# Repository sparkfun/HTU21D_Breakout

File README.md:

**NOTE:** *This product has been retired from our catalog. If you are looking for more up-to-date info, please check out some of these resources to see how other users are still hacking and improving on this product.*
* *[SparkFun Forum](https://forum.sparkfun.com/)*
* *[Comments Here on GitHub](https://github.com/sparkfun/HTU21D_Breakout/issues)*

*We recommend looking at the [Si7021](https://www.sparkfun.com/products/13763), which is a drop-in replacement for the HTU21D. It uses the same address and methods to read the sensor.*

SparkFun Humidity and Temperature Sensor Breakout - HTU21D
===========================================================

[*SparkFun Humidity and Temperature Sensor Breakout - HTU21D (SEN-12064)*](https://www.sparkfun.com/products/12064)

This is a breadboard friendly breakout board for the Measurement Specialties high-precision, low-power digital humidity sensor.

Repository Contents
-------------------
* **/Firmware** - Example code 
* **/Hardware** - Eagle design files (.brd, .sch)
* **/Libraries** - Libraries for use with the <PRODUCT NAME>
* **/Production** - Production panel files (.brd)

Documentation
--------------
* **[Library](https://github.com/sparkfun/SparkFun_HTU21D_Breakout_Arduino_Library)** - Arduino library for the HTU21D.
* **[Hookup Guide](https://learn.sparkfun.com/tutorials/htu21d-humidity-sensor-hookup-guide)** - Basic hookup guide for the HTU21D.
* **[SparkFun Fritzing repo](https://github.com/sparkfun/Fritzing_Parts)** - Fritzing diagrams for SparkFun products.
* **[SparkFun 3D Model repo](https://github.com/sparkfun/3D_Models)** - 3D models of SparkFun products. 

License Information
-------------------
This product is _**open source**_! 

The **hardware** is released under [Creative Commons ShareAlike 4.0 International](https://creativecommons.org/licenses/by-sa/4.0/).

The **code** is beerware; if you see me (or any other SparkFun employee) at the local, and you've found our code helpful, please buy us a round!

Please use, reuse, and modify these files as you see fit. Please maintain attribution to SparkFun Electronics and release anything derivative under the same license.

Distributed as-is; no warranty is given.

- Your friends at SparkFun.

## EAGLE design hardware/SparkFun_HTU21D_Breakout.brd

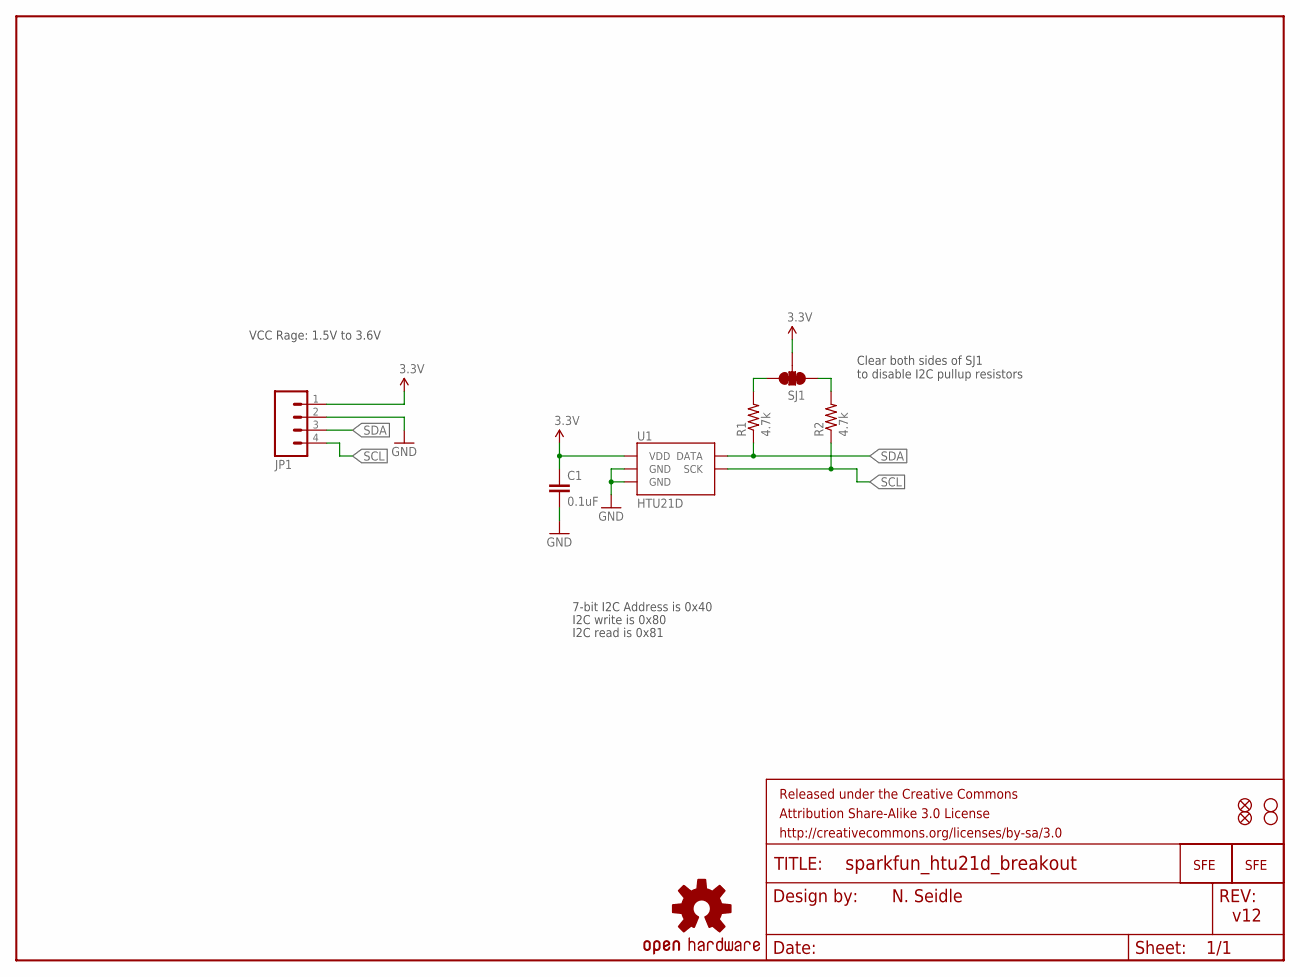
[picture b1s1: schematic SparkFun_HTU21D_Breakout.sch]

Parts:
C1: 0.1uF; 0603-CAP
FRAME2: FRAME-LETTER; CREATIVE_COMMONS
JP1: M04PTH; 1X04
JP2: LOGO-SFENW2; SFE-NEW-WEB
JP3, JP4: FIDUCIALUFIDUCIAL; MICRO-FIDUCIAL
LOGO1: LOGO-SFESK; SFE-LOGO-FLAME
LOGO2: OSHW-LOGOS; OSHW-LOGO-S
R1, R2: 4.7k; 0603-RES
SJ1: SOLDERJUMPER_2WAYPASTE1&2&3; SJ_3_PASTE1&2&3
STANDOFF1, STANDOFF2: STAND-OFF
U1: HTU21D

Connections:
3.3V: C1.1, JP1.1, SJ1.2, U1.VDD
GND: C1.2, JP1.2, U1.7 (GND), U1.GND
unnamed: R1.2, SJ1.3
unnamed: R2.2, SJ1.1
SCL: JP1.4, R2.1, U1.SCK
SDA: JP1.3, R1.1, U1.DATA

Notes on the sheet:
N. Seidle
Clear both sides of SJ1 to disable I2C pullup resistors
VCC Rage: 1.5V to 3.6V
7-bit I2C Address is 0x40
I2C write is 0x80
I2C read is 0x81
v12

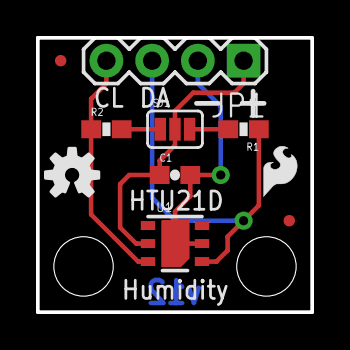
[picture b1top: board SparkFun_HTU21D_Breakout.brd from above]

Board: 2 copper layers, 15.2 x 15.2 mm, 14 parts (1 on the bottom side), 6 nets.

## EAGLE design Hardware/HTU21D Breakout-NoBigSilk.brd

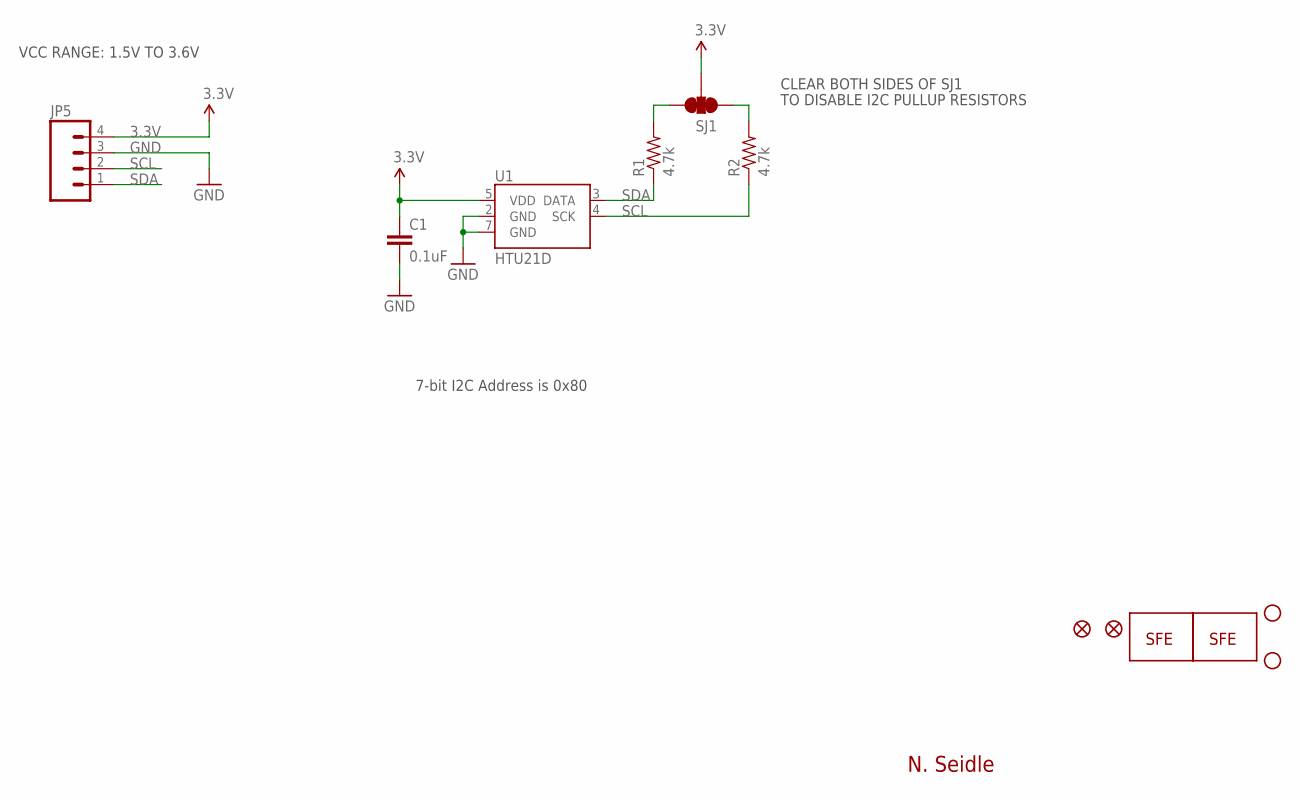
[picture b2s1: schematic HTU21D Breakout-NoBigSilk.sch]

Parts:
C1: 0.1uF; 0402-CAP
JP2: LOGO-SFENW2; SFE-NEW-WEB
JP3, JP4: FIDUCIALUFIDUCIAL; MICRO-FIDUCIAL
JP5: M04PTH; 1X04
LOGO1: LOGO-SFESK; SFE-LOGO-FLAME
R1, R2: 4.7k; 0402-RES
SJ1: SOLDERJUMPER_2WAYPASTE1&2&3; SJ_3_PASTE1&2&3
STANDOFF1, STANDOFF2: STAND-OFF
U1: HTU21D

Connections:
3.3V: C1.1, JP5.4, SJ1.2, U1.5 (VDD)
GND: C1.2, JP5.3, U1.2 (GND), U1.7 (GND)
unnamed: R1.2, SJ1.3
unnamed: R2.2, SJ1.1
SCL: JP5.2, R2.1, U1.4 (SCK)
SDA: JP5.1, R1.1, U1.3 (DATA)

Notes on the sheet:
N. Seidle
CLEAR BOTH SIDES OF SJ1
TO DISABLE I2C PULLUP RESISTORS
VCC RANGE: 1.5V TO 3.6V
7-bit I2C Address is 0x80

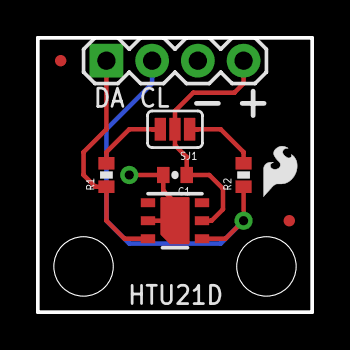
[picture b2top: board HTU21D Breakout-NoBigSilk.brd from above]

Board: 2 copper layers, 15.2 x 15.2 mm, 12 parts (1 on the bottom side), 6 nets.

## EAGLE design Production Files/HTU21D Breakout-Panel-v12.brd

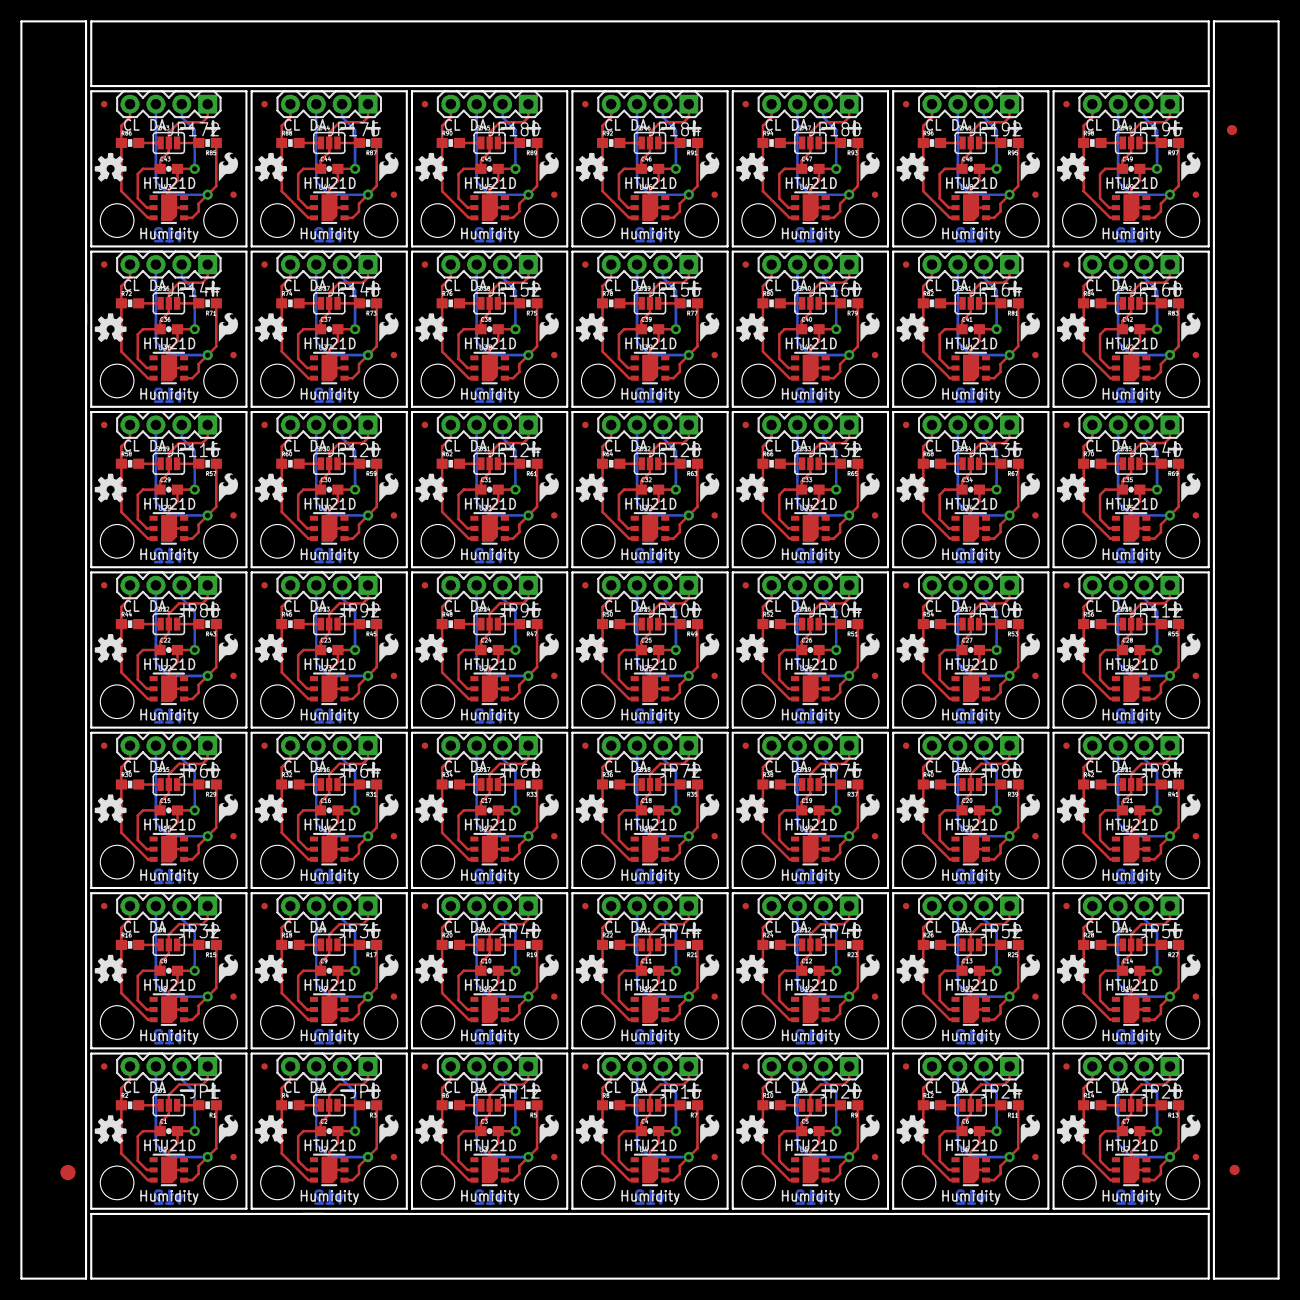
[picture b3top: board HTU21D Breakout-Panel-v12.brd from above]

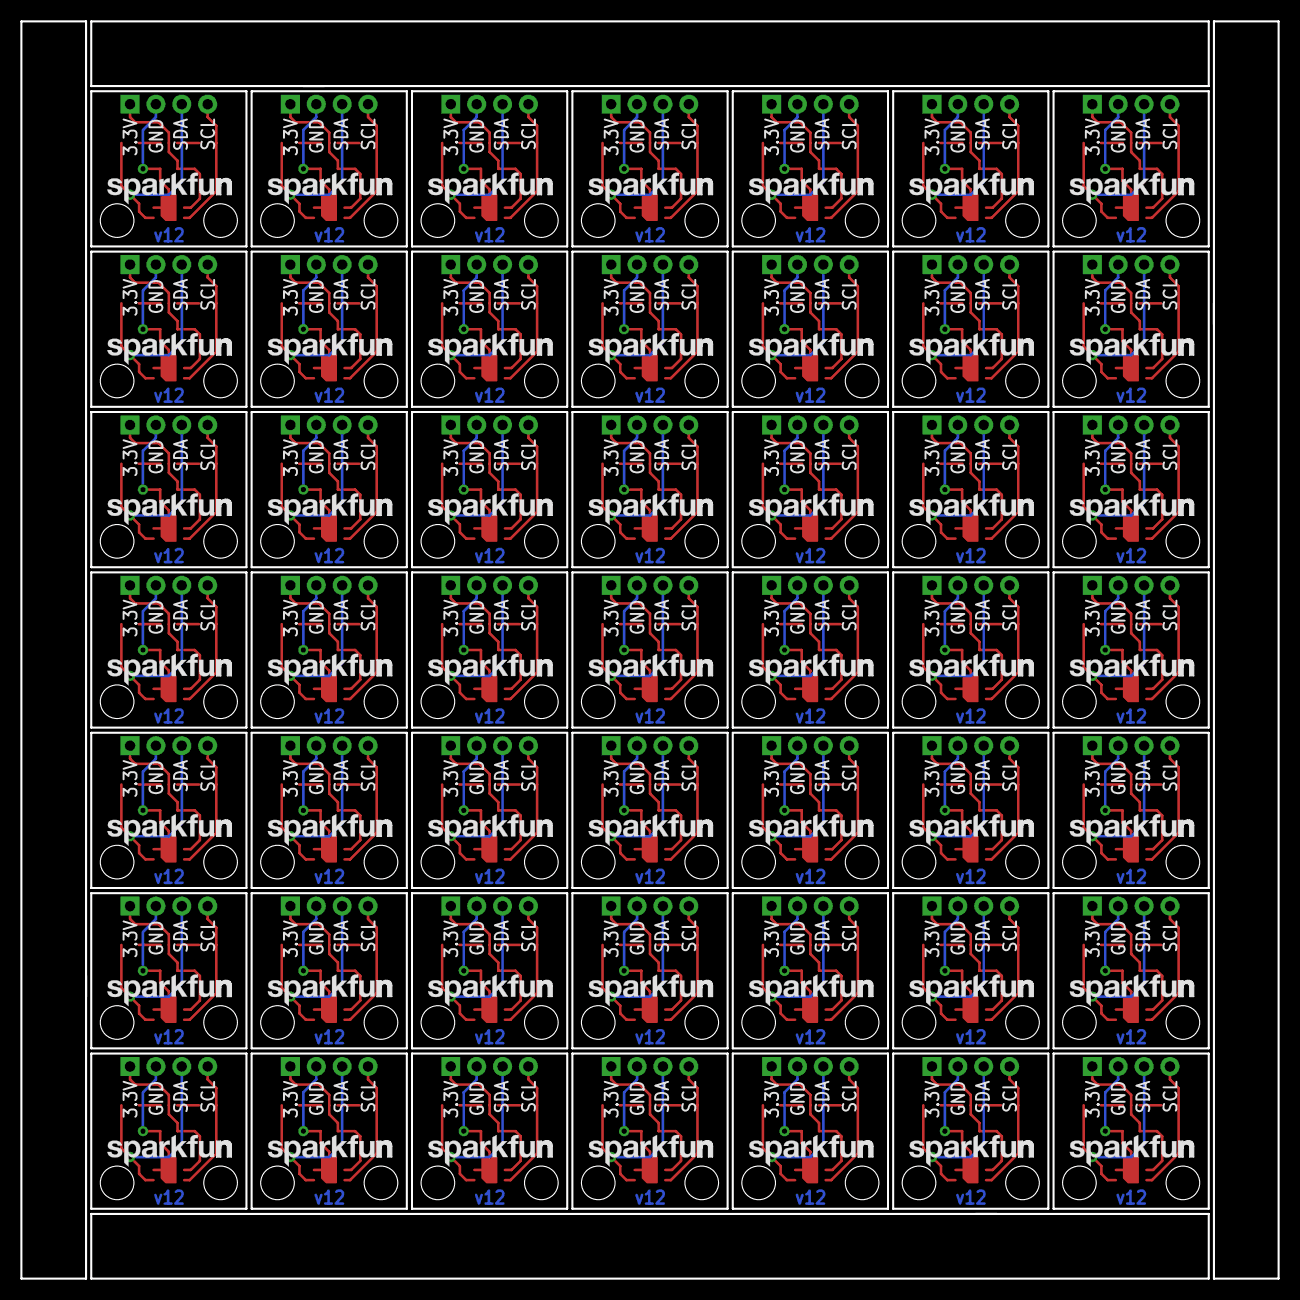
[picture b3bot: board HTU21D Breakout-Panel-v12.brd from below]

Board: 2 copper layers, 123.4 x 123.4 mm, 640 parts (49 on the bottom side), 294 nets.

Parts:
C1, C2, C3, C4, C5, C6, C7, C8, C9, C10, C11, C12, C13, C14, C15, C16, C17, C18, C19, C20, C21, C22, C23, C24, C25, C26, C27, C28, C29, C30, C31, C32, C33, C34, C35, C36, C37, C38, C39, C40, C41, C42, C43, C44, C45, C46, C47, C48, C49: 0.1uF; 0603-CAP
E$1: FIDUCIAL-1.5X3
E$4, E$5: FIDUCIAL-1X2
JP1, JP8, JP12, JP16, JP20, JP24, JP28, JP32, JP36, JP40, JP44, JP48, JP52, JP56, JP60, JP64, JP68, JP72, JP76, JP80, JP84, JP88, JP92, JP96, JP100, JP104, JP108, JP112, JP116, JP120, JP124, JP128, JP132, JP136, JP140, JP144, JP148, JP152, JP156, JP160, JP164, JP168, JP172, JP176, JP180, JP184, JP188, JP192, JP196: 1X04
JP2, JP5, JP9, JP13, JP17, JP21, JP25, JP29, JP33, JP37, JP41, JP45, JP49, JP53, JP57, JP61, JP65, JP69, JP73, JP77, JP81, JP85, JP89, JP93, JP97, JP101, JP105, JP109, JP113, JP117, JP121, JP125, JP129, JP133, JP137, JP141, JP145, JP149, JP153, JP157, JP161, JP165, JP169, JP173, JP177, JP181, JP185, JP189, JP193: LOGO-SFENW2; SFE-NEW-WEB
JP3, JP4, JP6, JP7, JP10, JP11, JP14, JP15, JP18, JP19, JP22, JP23, JP26, JP27, JP30, JP31, JP34, JP35, JP38, JP39, JP42, JP43, JP46, JP47, JP50, JP51, JP54, JP55, JP58, JP59, JP62, JP63, JP66, JP67, JP70, JP71, JP74, JP75, JP78, JP79, JP82, JP83, JP86, JP87, JP90, JP91, JP94, JP95, JP98, JP99, JP102, JP103, JP106, JP107, JP110, JP111, JP114, JP115, JP118, JP119, JP122, JP123, JP126, JP127, JP130, JP131, JP134, JP135, JP138, JP139, JP142, JP143, JP146, JP147, JP150, JP151, JP154, JP155, JP158, JP159, JP162, JP163, JP166, JP167, JP170, JP171, JP174, JP175, JP178, JP179, JP182, JP183, JP186, JP187, JP190, JP191, JP194, JP195: FIDUCIALUFIDUCIAL; MICRO-FIDUCIAL
LOGO1, LOGO3, LOGO5, LOGO7, LOGO9, LOGO11, LOGO13, LOGO15, LOGO17, LOGO19, LOGO21, LOGO23, LOGO25, LOGO27, LOGO29, LOGO31, LOGO33, LOGO35, LOGO37, LOGO39, LOGO41, LOGO43, LOGO45, LOGO47, LOGO49, LOGO51, LOGO53, LOGO55, LOGO57, LOGO59, LOGO61, LOGO63, LOGO65, LOGO67, LOGO69, LOGO71, LOGO73, LOGO75, LOGO77, LOGO79, LOGO81, LOGO83, LOGO85, LOGO87, LOGO89, LOGO91, LOGO93, LOGO95, LOGO97: LOGO-SFESK; SFE-LOGO-FLAME
LOGO2, LOGO4, LOGO6, LOGO8, LOGO10, LOGO12, LOGO14, LOGO16, LOGO18, LOGO20, LOGO22, LOGO24, LOGO26, LOGO28, LOGO30, LOGO32, LOGO34, LOGO36, LOGO38, LOGO40, LOGO42, LOGO44, LOGO46, LOGO48, LOGO50, LOGO52, LOGO54, LOGO56, LOGO58, LOGO60, LOGO62, LOGO64, LOGO66, LOGO68, LOGO70, LOGO72, LOGO74, LOGO76, LOGO78, LOGO80, LOGO82, LOGO84, LOGO86, LOGO88, LOGO90, LOGO92, LOGO94, LOGO96, LOGO98: OSHW-LOGOS; OSHW-LOGO-S
R1, R2, R3, R4, R5, R6, R7, R8, R9, R10, R11, R12, R13, R14, R15, R16, R17, R18, R19, R20, R21, R22, R23, R24, R25, R26, R27, R28, R29, R30, R31, R32, R33, R34, R35, R36, R37, R38, R39, R40, R41, R42, R43, R44, R45, R46, R47, R48, R49, R50, R51, R52, R53, R54, R55, R56, R57, R58, R59, R60, R61, R62, R63, R64, R65, R66, R67, R68, R69, R70, R71, R72, R73, R74, R75, R76, R77, R78, R79, R80, R81, R82, R83, R84, R85, R86, R87, R88, R89, R90, R91, R92, R93, R94, R95, R96, R97, R98: 4.7k; 0603-RES
SJ1, SJ2, SJ3, SJ4, SJ5, SJ6, SJ7, SJ8, SJ9, SJ10, SJ11, SJ12, SJ13, SJ14, SJ15, SJ16, SJ17, SJ18, SJ19, SJ20, SJ21, SJ22, SJ23, SJ24, SJ25, SJ26, SJ27, SJ28, SJ29, SJ30, SJ31, SJ32, SJ33, SJ34, SJ35, SJ36, SJ37, SJ38, SJ39, SJ40, SJ41, SJ42, SJ43, SJ44, SJ45, SJ46, SJ47, SJ48, SJ49: SJ_3_PASTE1&2&3
STANDOFF1, STANDOFF2, STANDOFF3, STANDOFF4, STANDOFF5, STANDOFF6, STANDOFF7, STANDOFF8, STANDOFF9, STANDOFF10, STANDOFF11, STANDOFF12, STANDOFF13, STANDOFF14, STANDOFF15, STANDOFF16, STANDOFF17, STANDOFF18, STANDOFF19, STANDOFF20, STANDOFF21, STANDOFF22, STANDOFF23, STANDOFF24, STANDOFF25, STANDOFF26, STANDOFF27, STANDOFF28, STANDOFF29, STANDOFF30, STANDOFF31, STANDOFF32, STANDOFF33, STANDOFF34, STANDOFF35, STANDOFF36, STANDOFF37, STANDOFF38, STANDOFF39, STANDOFF40, STANDOFF41, STANDOFF42, STANDOFF43, STANDOFF44, STANDOFF45, STANDOFF46, STANDOFF47, STANDOFF48, STANDOFF49, STANDOFF50, STANDOFF51, STANDOFF52, STANDOFF53, STANDOFF54, STANDOFF55, STANDOFF56, STANDOFF57, STANDOFF58, STANDOFF59, STANDOFF60, STANDOFF61, STANDOFF62, STANDOFF63, STANDOFF64, STANDOFF65, STANDOFF66, STANDOFF67, STANDOFF68, STANDOFF69, STANDOFF70, STANDOFF71, STANDOFF72, STANDOFF73, STANDOFF74, STANDOFF75, STANDOFF76, STANDOFF77, STANDOFF78, STANDOFF79, STANDOFF80, STANDOFF81, STANDOFF82, STANDOFF83, STANDOFF84, STANDOFF85, STANDOFF86, STANDOFF87, STANDOFF88, STANDOFF89, STANDOFF90, STANDOFF91, STANDOFF92, STANDOFF93, STANDOFF94, STANDOFF95, STANDOFF96, STANDOFF97, STANDOFF98: STAND-OFF
U1, U2, U3, U4, U5, U6, U7, U8, U9, U10, U11, U12, U13, U14, U15, U16, U17, U18, U19, U20, U21, U22, U23, U24, U25, U26, U27, U28, U29, U30, U31, U32, U33, U34, U35, U36, U37, U38, U39, U40, U41, U42, U43, U44, U45, U46, U47, U48, U49: HTU21D

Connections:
3.3V: C1.1, JP1.1, SJ1.2, U1.VDD
3.3V1: C2.1, JP8.1, SJ2.2, U2.VDD
3.3V2: C3.1, JP12.1, SJ3.2, U3.VDD
3.3V3: C4.1, JP16.1, SJ4.2, U4.VDD
3.3V4: C5.1, JP20.1, SJ5.2, U5.VDD
3.3V5: C6.1, JP24.1, SJ6.2, U6.VDD
3.3V6: C7.1, JP28.1, SJ7.2, U7.VDD
3.3V7: C8.1, JP32.1, SJ8.2, U8.VDD
3.3V8: C9.1, JP36.1, SJ9.2, U9.VDD
3.3V9: C10.1, JP40.1, SJ10.2, U10.VDD
3.3V10: C11.1, JP44.1, SJ11.2, U11.VDD
3.3V11: C12.1, JP48.1, SJ12.2, U12.VDD
3.3V12: C13.1, JP52.1, SJ13.2, U13.VDD
3.3V13: C14.1, JP56.1, SJ14.2, U14.VDD
3.3V14: C15.1, JP60.1, SJ15.2, U15.VDD
3.3V15: C16.1, JP64.1, SJ16.2, U16.VDD
3.3V16: C17.1, JP68.1, SJ17.2, U17.VDD
3.3V17: C18.1, JP72.1, SJ18.2, U18.VDD
3.3V18: C19.1, JP76.1, SJ19.2, U19.VDD
3.3V19: C20.1, JP80.1, SJ20.2, U20.VDD
3.3V20: C21.1, JP84.1, SJ21.2, U21.VDD
3.3V21: C22.1, JP88.1, SJ22.2, U22.VDD
3.3V22: C23.1, JP92.1, SJ23.2, U23.VDD
3.3V23: C24.1, JP96.1, SJ24.2, U24.VDD
3.3V24: C25.1, JP100.1, SJ25.2, U25.VDD
3.3V25: C26.1, JP104.1, SJ26.2, U26.VDD
3.3V26: C27.1, JP108.1, SJ27.2, U27.VDD
3.3V27: C28.1, JP112.1, SJ28.2, U28.VDD
3.3V28: C29.1, JP116.1, SJ29.2, U29.VDD
3.3V29: C30.1, JP120.1, SJ30.2, U30.VDD
3.3V30: C31.1, JP124.1, SJ31.2, U31.VDD
3.3V31: C32.1, JP128.1, SJ32.2, U32.VDD
3.3V32: C33.1, JP132.1, SJ33.2, U33.VDD
3.3V33: C34.1, JP136.1, SJ34.2, U34.VDD
3.3V34: C35.1, JP140.1, SJ35.2, U35.VDD
3.3V35: C36.1, JP144.1, SJ36.2, U36.VDD
3.3V36: C37.1, JP148.1, SJ37.2, U37.VDD
3.3V37: C38.1, JP152.1, SJ38.2, U38.VDD
3.3V38: C39.1, JP156.1, SJ39.2, U39.VDD
3.3V39: C40.1, JP160.1, SJ40.2, U40.VDD
3.3V40: C41.1, JP164.1, SJ41.2, U41.VDD
3.3V41: C42.1, JP168.1, SJ42.2, U42.VDD
3.3V42: C43.1, JP172.1, SJ43.2, U43.VDD
3.3V43: C44.1, JP176.1, SJ44.2, U44.VDD
3.3V44: C45.1, JP180.1, SJ45.2, U45.VDD
3.3V45: C46.1, JP184.1, SJ46.2, U46.VDD
3.3V46: C47.1, JP188.1, SJ47.2, U47.VDD
3.3V47: C48.1, JP192.1, SJ48.2, U48.VDD
3.3V48: C49.1, JP196.1, SJ49.2, U49.VDD
GND: C1.2, JP1.2, U1.7, U1.GND
GND1: C2.2, JP8.2, U2.7, U2.GND
GND2: C3.2, JP12.2, U3.7, U3.GND
GND3: C4.2, JP16.2, U4.7, U4.GND
GND4: C5.2, JP20.2, U5.7, U5.GND
GND5: C6.2, JP24.2, U6.7, U6.GND
GND6: C7.2, JP28.2, U7.7, U7.GND
GND7: C8.2, JP32.2, U8.7, U8.GND
GND8: C9.2, JP36.2, U9.7, U9.GND
GND9: C10.2, JP40.2, U10.7, U10.GND
GND10: C11.2, JP44.2, U11.7, U11.GND
GND11: C12.2, JP48.2, U12.7, U12.GND
GND12: C13.2, JP52.2, U13.7, U13.GND
GND13: C14.2, JP56.2, U14.7, U14.GND
GND14: C15.2, JP60.2, U15.7, U15.GND
GND15: C16.2, JP64.2, U16.7, U16.GND
GND16: C17.2, JP68.2, U17.7, U17.GND
GND17: C18.2, JP72.2, U18.7, U18.GND
GND18: C19.2, JP76.2, U19.7, U19.GND
GND19: C20.2, JP80.2, U20.7, U20.GND
GND20: C21.2, JP84.2, U21.7, U21.GND
GND21: C22.2, JP88.2, U22.7, U22.GND
GND22: C23.2, JP92.2, U23.7, U23.GND
GND23: C24.2, JP96.2, U24.7, U24.GND
GND24: C25.2, JP100.2, U25.7, U25.GND
GND25: C26.2, JP104.2, U26.7, U26.GND
GND26: C27.2, JP108.2, U27.7, U27.GND
GND27: C28.2, JP112.2, U28.7, U28.GND
GND28: C29.2, JP116.2, U29.7, U29.GND
GND29: C30.2, JP120.2, U30.7, U30.GND
GND30: C31.2, JP124.2, U31.7, U31.GND
GND31: C32.2, JP128.2, U32.7, U32.GND
GND32: C33.2, JP132.2, U33.7, U33.GND
GND33: C34.2, JP136.2, U34.7, U34.GND
GND34: C35.2, JP140.2, U35.7, U35.GND
GND35: C36.2, JP144.2, U36.7, U36.GND
GND36: C37.2, JP148.2, U37.7, U37.GND
GND37: C38.2, JP152.2, U38.7, U38.GND
GND38: C39.2, JP156.2, U39.7, U39.GND
GND39: C40.2, JP160.2, U40.7, U40.GND
GND40: C41.2, JP164.2, U41.7, U41.GND
GND41: C42.2, JP168.2, U42.7, U42.GND
GND42: C43.2, JP172.2, U43.7, U43.GND
GND43: C44.2, JP176.2, U44.7, U44.GND
GND44: C45.2, JP180.2, U45.7, U45.GND
GND45: C46.2, JP184.2, U46.7, U46.GND
GND46: C47.2, JP188.2, U47.7, U47.GND
GND47: C48.2, JP192.2, U48.7, U48.GND
GND48: C49.2, JP196.2, U49.7, U49.GND
unnamed: R1.2, SJ1.3
unnamed: R2.2, SJ1.1
unnamed: R3.2, SJ2.3
unnamed: R4.2, SJ2.1
unnamed: R5.2, SJ3.3
unnamed: R6.2, SJ3.1
unnamed: R7.2, SJ4.3
unnamed: R8.2, SJ4.1
unnamed: R9.2, SJ5.3
unnamed: R10.2, SJ5.1
unnamed: R11.2, SJ6.3
unnamed: R12.2, SJ6.1
unnamed: R13.2, SJ7.3
unnamed: R14.2, SJ7.1
unnamed: R15.2, SJ8.3
unnamed: R16.2, SJ8.1
unnamed: R17.2, SJ9.3
unnamed: R18.2, SJ9.1
unnamed: R19.2, SJ10.3
unnamed: R20.2, SJ10.1
unnamed: R21.2, SJ11.3
unnamed: R22.2, SJ11.1
unnamed: R23.2, SJ12.3
unnamed: R24.2, SJ12.1
unnamed: R25.2, SJ13.3
unnamed: R26.2, SJ13.1
unnamed: R27.2, SJ14.3
unnamed: R28.2, SJ14.1
unnamed: R29.2, SJ15.3
unnamed: R30.2, SJ15.1
unnamed: R31.2, SJ16.3
unnamed: R32.2, SJ16.1
unnamed: R33.2, SJ17.3
unnamed: R34.2, SJ17.1
unnamed: R35.2, SJ18.3
unnamed: R36.2, SJ18.1
unnamed: R37.2, SJ19.3
unnamed: R38.2, SJ19.1
unnamed: R39.2, SJ20.3
unnamed: R40.2, SJ20.1
unnamed: R41.2, SJ21.3
unnamed: R42.2, SJ21.1
unnamed: R43.2, SJ22.3
unnamed: R44.2, SJ22.1
unnamed: R45.2, SJ23.3
unnamed: R46.2, SJ23.1
unnamed: R47.2, SJ24.3
unnamed: R48.2, SJ24.1
unnamed: R49.2, SJ25.3
unnamed: R50.2, SJ25.1
unnamed: R51.2, SJ26.3
unnamed: R52.2, SJ26.1
unnamed: R53.2, SJ27.3
unnamed: R54.2, SJ27.1
unnamed: R55.2, SJ28.3
unnamed: R56.2, SJ28.1
unnamed: R57.2, SJ29.3
unnamed: R58.2, SJ29.1
unnamed: R59.2, SJ30.3
unnamed: R60.2, SJ30.1
unnamed: R61.2, SJ31.3
unnamed: R62.2, SJ31.1
unnamed: R63.2, SJ32.3
unnamed: R64.2, SJ32.1
unnamed: R65.2, SJ33.3
unnamed: R66.2, SJ33.1
unnamed: R67.2, SJ34.3
unnamed: R68.2, SJ34.1
unnamed: R69.2, SJ35.3
unnamed: R70.2, SJ35.1
unnamed: R71.2, SJ36.3
unnamed: R72.2, SJ36.1
unnamed: R73.2, SJ37.3
unnamed: R74.2, SJ37.1
unnamed: R75.2, SJ38.3
unnamed: R76.2, SJ38.1
unnamed: R77.2, SJ39.3
unnamed: R78.2, SJ39.1
unnamed: R79.2, SJ40.3
unnamed: R80.2, SJ40.1
unnamed: R81.2, SJ41.3
unnamed: R82.2, SJ41.1
unnamed: R83.2, SJ42.3
unnamed: R84.2, SJ42.1
unnamed: R85.2, SJ43.3
unnamed: R86.2, SJ43.1
unnamed: R87.2, SJ44.3
unnamed: R88.2, SJ44.1
unnamed: R89.2, SJ45.3
unnamed: R90.2, SJ45.1
unnamed: R91.2, SJ46.3
unnamed: R92.2, SJ46.1
unnamed: R93.2, SJ47.3
unnamed: R94.2, SJ47.1
unnamed: R95.2, SJ48.3
unnamed: R96.2, SJ48.1
unnamed: R97.2, SJ49.3
unnamed: R98.2, SJ49.1
SCL: JP1.4, R2.1, U1.SCK
SCL1: JP8.4, R4.1, U2.SCK
SCL2: JP12.4, R6.1, U3.SCK
SCL3: JP16.4, R8.1, U4.SCK
SCL4: JP20.4, R10.1, U5.SCK
SCL5: JP24.4, R12.1, U6.SCK
SCL6: JP28.4, R14.1, U7.SCK
SCL7: JP32.4, R16.1, U8.SCK
SCL8: JP36.4, R18.1, U9.SCK
SCL9: JP40.4, R20.1, U10.SCK
SCL10: JP44.4, R22.1, U11.SCK
SCL11: JP48.4, R24.1, U12.SCK
SCL12: JP52.4, R26.1, U13.SCK
SCL13: JP56.4, R28.1, U14.SCK
SCL14: JP60.4, R30.1, U15.SCK
SCL15: JP64.4, R32.1, U16.SCK
SCL16: JP68.4, R34.1, U17.SCK
SCL17: JP72.4, R36.1, U18.SCK
SCL18: JP76.4, R38.1, U19.SCK
SCL19: JP80.4, R40.1, U20.SCK
SCL20: JP84.4, R42.1, U21.SCK
SCL21: JP88.4, R44.1, U22.SCK
SCL22: JP92.4, R46.1, U23.SCK
SCL23: JP96.4, R48.1, U24.SCK
SCL24: JP100.4, R50.1, U25.SCK
SCL25: JP104.4, R52.1, U26.SCK
SCL26: JP108.4, R54.1, U27.SCK
SCL27: JP112.4, R56.1, U28.SCK
SCL28: JP116.4, R58.1, U29.SCK
SCL29: JP120.4, R60.1, U30.SCK
SCL30: JP124.4, R62.1, U31.SCK
SCL31: JP128.4, R64.1, U32.SCK
SCL32: JP132.4, R66.1, U33.SCK
SCL33: JP136.4, R68.1, U34.SCK
SCL34: JP140.4, R70.1, U35.SCK
SCL35: JP144.4, R72.1, U36.SCK
SCL36: JP148.4, R74.1, U37.SCK
SCL37: JP152.4, R76.1, U38.SCK
SCL38: JP156.4, R78.1, U39.SCK
SCL39: JP160.4, R80.1, U40.SCK
SCL40: JP164.4, R82.1, U41.SCK
SCL41: JP168.4, R84.1, U42.SCK
SCL42: JP172.4, R86.1, U43.SCK
SCL43: JP176.4, R88.1, U44.SCK
SCL44: JP180.4, R90.1, U45.SCK
SCL45: JP184.4, R92.1, U46.SCK
SCL46: JP188.4, R94.1, U47.SCK
SCL47: JP192.4, R96.1, U48.SCK
SCL48: JP196.4, R98.1, U49.SCK
SDA: JP1.3, R1.1, U1.DATA
SDA1: JP8.3, R3.1, U2.DATA
SDA2: JP12.3, R5.1, U3.DATA
SDA3: JP16.3, R7.1, U4.DATA
SDA4: JP20.3, R9.1, U5.DATA
SDA5: JP24.3, R11.1, U6.DATA
SDA6: JP28.3, R13.1, U7.DATA
SDA7: JP32.3, R15.1, U8.DATA
SDA8: JP36.3, R17.1, U9.DATA
SDA9: JP40.3, R19.1, U10.DATA
SDA10: JP44.3, R21.1, U11.DATA
SDA11: JP48.3, R23.1, U12.DATA
SDA12: JP52.3, R25.1, U13.DATA
SDA13: JP56.3, R27.1, U14.DATA
SDA14: JP60.3, R29.1, U15.DATA
SDA15: JP64.3, R31.1, U16.DATA
SDA16: JP68.3, R33.1, U17.DATA
SDA17: JP72.3, R35.1, U18.DATA
SDA18: JP76.3, R37.1, U19.DATA
SDA19: JP80.3, R39.1, U20.DATA
SDA20: JP84.3, R41.1, U21.DATA
SDA21: JP88.3, R43.1, U22.DATA
SDA22: JP92.3, R45.1, U23.DATA
SDA23: JP96.3, R47.1, U24.DATA
SDA24: JP100.3, R49.1, U25.DATA
SDA25: JP104.3, R51.1, U26.DATA
SDA26: JP108.3, R53.1, U27.DATA
SDA27: JP112.3, R55.1, U28.DATA
SDA28: JP116.3, R57.1, U29.DATA
SDA29: JP120.3, R59.1, U30.DATA
SDA30: JP124.3, R61.1, U31.DATA
SDA31: JP128.3, R63.1, U32.DATA
SDA32: JP132.3, R65.1, U33.DATA
SDA33: JP136.3, R67.1, U34.DATA
SDA34: JP140.3, R69.1, U35.DATA
SDA35: JP144.3, R71.1, U36.DATA
SDA36: JP148.3, R73.1, U37.DATA
SDA37: JP152.3, R75.1, U38.DATA
SDA38: JP156.3, R77.1, U39.DATA
SDA39: JP160.3, R79.1, U40.DATA
SDA40: JP164.3, R81.1, U41.DATA
SDA41: JP168.3, R83.1, U42.DATA
SDA42: JP172.3, R85.1, U43.DATA
SDA43: JP176.3, R87.1, U44.DATA
SDA44: JP180.3, R89.1, U45.DATA
SDA45: JP184.3, R91.1, U46.DATA
SDA46: JP188.3, R93.1, U47.DATA
SDA47: JP192.3, R95.1, U48.DATA
SDA48: JP196.3, R97.1, U49.DATA

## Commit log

2013-09-16 Initial commit. Example code doesn't yet work.
    Board layout is solid, but example code is still in the works.
2013-09-16 More changes to the code and repo.
2013-09-17 Re-routing post review with engineering recommendations.
    Moved to 0603 footprints. Removed ground planes to align with datasheet
    thermal recommendations. Added OSHW logo. Updated frame to CC 3.0. Added
    revision code to bottom copper.
2013-09-17 Added flags on data lines to schematic.
2013-09-20 Corrected a reversed the footprint.
    Arg! I forgot to invert the footprint. Corrected.
2013-09-20 Updated version number on layout to v11.
2013-09-22 Improving the example code
2013-09-22 Adding HTU21D library
2013-09-22 Rename library ino example
2013-09-25 Correcting directory structure.
2013-09-25 Adding connection info to example.
2013-10-11 Cleaning up example code.
2013-10-12 Example code, layout, and library working.
    Added small 'humidity' text to board.
2013-10-14 Panel Created
2013-10-15 Corrected tcream on footprint on v12.
    Tcream was too small on center pad. Updated board with latest lib fixed
    it.
2013-10-16 Recreated Panel
2013-11-11 Adding fritzing part
2013-11-11 Correcting directory structure
2013-11-12 Added comments to example code.
2013-11-14 Updated readme. Cosmetic changes to schematic.
2013-11-22 Update README.md
    Fixing product urls.
2014-01-16 Updating example in library to use 330 inline resistors at 5V
2014-08-19 Cleared compiler warnings - begin() does not return a value -- changed the return type to "void" - explicitly cast initialization value to float - used binary constant from Arduino's binary.h, instea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
2015-04-24 Squashed 'Libraries/Arduint/' content from commit bc1f3e8
    git-subtree-dir: Libraries/Arduint
    git-subtree-split: bc1f3e8de67acc1b1682489c53e6bba6a2ea8caa
2015-04-24 Adding readme, fixing misspelled directory.
2015-04-24 One more readme tweak.
2015-04-24 Re-fixing misspelled directory.
2015-05-14 Updating firmware files, fixing naming issues
2015-05-14 Fixing readme links, production directory name, removing Fritzing diagrams to main Fritzing repo
2015-05-14 Fixing subtree clash
2015-05-14 Squashed 'Libraries/Arduino/' content from commit db0d027
    git-subtree-dir: Libraries/Arduino
    git-subtree-split: db0d027d4c8ff2eca0a532afa359a7c6fcbcc55f
2015-07-13 Squashed 'Libraries/Arduino/' changes from db0d027..2ff23bf
    2ff23bf Update library.properties
    git-subtree-dir: Libraries/Arduino
    git-subtree-split: 2ff23bff475d03202598204878445e841019ae69
2015-08-04 Squashed 'Libraries/Arduino/' changes from 2ff23bf..fdacea6
    fdacea6 Fixing library name typo
    git-subtree-dir: Libraries/Arduino
    git-subtree-split: fdacea6cd009e2d1a5eddf22aaa42cfad06e464d
2016-10-24 Squashed 'Libraries/Arduino/' changes from fdacea6..515623d
    515623d Update to genericized definition of I2C port
    b04a2a0 Read functions now return errors correctly
    f1379a0 Correcting RaNo99 issue 4. Changing variable names to fit Arduino style guide.
    93d8ead Fixing typo in IC define. Non-critical.
    0295c8c Updating lib ver #. Splitting baruch's code into a separate example.
    08e008e Merge pull request #3 from baruch/master

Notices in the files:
parts and their libraries:
SparkFun-Electromechanical: Licensing: CC v3.0 Share-Alike You are welcome to use this library for commercial purposes.
SparkFun-Aesthetics: Released under the Creative Commons Attribution Share-Alike 3.0 License
SparkFun-Aesthetics: http://creativecommons.org/licenses/by-sa/3.0
